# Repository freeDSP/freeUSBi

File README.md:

# freeUSBi

BOARD STATUS: READY TO BE BUILT

MAIN COORDINATOR: [thebadseeds](https://github.com/thebadseeds)

The freeUSBi is a low-budget real-time programming device for the freeDSP and other DSP boards from Analog Devices. It is based on a CY7C68013A MINI BOARD combined with an adapter PCB (printed circuit board) that adds the possibility of realtime programming.
It has the same features as the Analog Devices USB interface (EVAL-ADUSB2EBZ), such as changing parameters while already using the freeDSP or easy changes of the schematic in SigmaStudio. You also can write your program to the EEPROM.

Please refer to the documentation for more information.

## License

This work and all other materials under https://github.com/freeDSP are licensed under a <a rel="license" href="http://creativecommons.org/licenses/by-sa/4.0/legalcode">Creative Commons Attribution Share-Alike 4.0 license</a>. This allows for both personal and commercial derivative works, as long as they credit freeDSP and release their designs under the same license.

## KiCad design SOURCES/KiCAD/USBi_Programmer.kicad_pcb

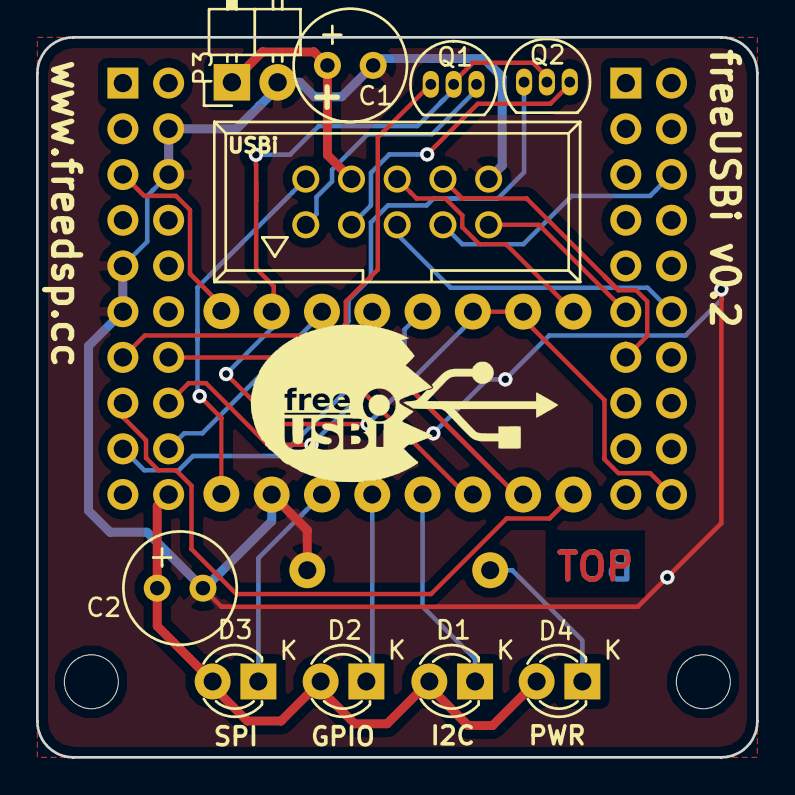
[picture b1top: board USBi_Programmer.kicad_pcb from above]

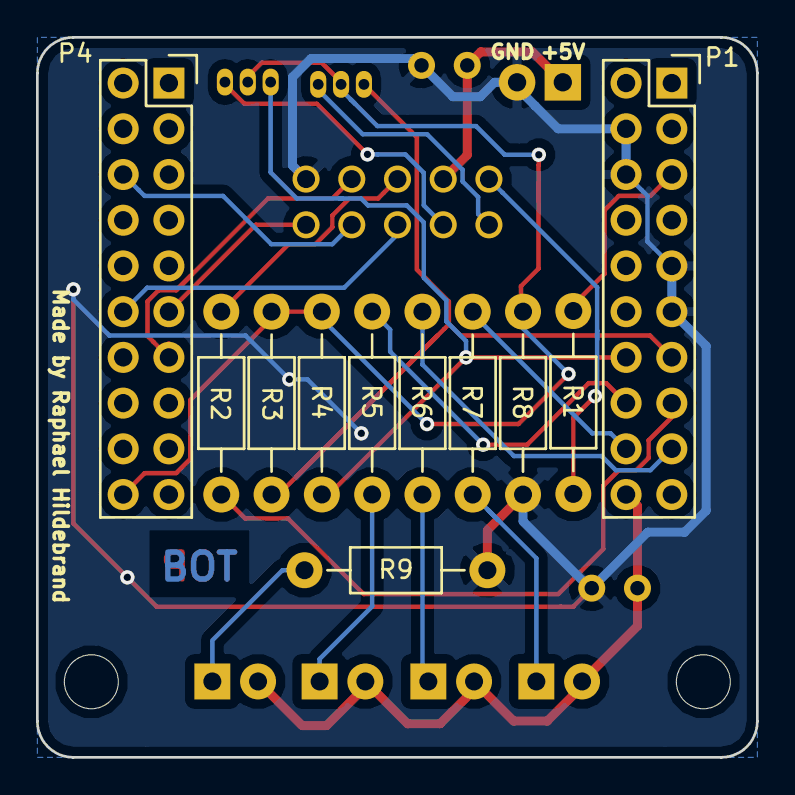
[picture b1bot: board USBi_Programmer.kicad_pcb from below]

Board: 2 copper layers, 40.0 x 40.0 mm, 21 parts (11 on the bottom side), 23 nets.

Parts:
C1, C2: 100u; Elko_vert_11.2x6.3mm_RM2.5_CopperClear
D1, D2, D3, D4: LED; LED-3MM
P1, P4: CONN_02X10; Socket_Strip_Straight_2x10
P2: CONN_02X05; VASCH5x2
P3: CONN_01X02; Pin_Header_Angled_1x02
Q1, Q2: Q_NMOS_DGS; TO-92_Inline_Narrow_Oval
R1: 49R9; Resistor_Horizontal_RM10mm
R2, R5, R6, R7, R9: 470R; Resistor_Horizontal_RM10mm
R3, R4: 10k; Resistor_Horizontal_RM10mm
R8: 1M; Resistor_Horizontal_RM10mm

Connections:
+3V3: C2.1, D1.2, D2.2, D3.2, D4.2, P1.20
+5VD: C1.1, P2.4, P3.1
BRD_~RESET: P2.6, R2.2
CCLK: P2.7, P4.6
CDATA: P2.8, P4.13
COUT: P2.5, P4.12
GND: C1.2, C2.2, P1.4, P1.6, P1.9, P1.11, P2.10, P3.2, R8.1, R9.2
LED_1: P1.16, R5.2
LED_2: P1.17, R6.2
LED_3: P1.18, R7.2
unnamed: D1.1, R5.1
unnamed: D2.1, R6.1
unnamed: D3.1, R7.1
unnamed: D4.1, R9.1
unnamed: P1.5, R1.1
unnamed: P1.15, R2.1
unnamed: P2.1, Q1.3
unnamed: P2.3, Q2.3
SCL: P1.13, Q1.1, R3.1
SDA: P1.14, Q2.1, R4.2
USB_CLK: P2.2, R1.2
USB_PWR_ON: P4.20, Q1.2, Q2.2, R3.2, R4.1, R8.2
~CLATCH1: P2.9, P4.11

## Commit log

2015-12-21 folder structure + initial sources V0.1
    added folder structure + initial sources V0.1
2015-12-21 Hardware configuration example for ADAU1701
2016-02-27 Create readme.md for testing link to GDOC documentation
2016-02-27 update link
2016-02-27 change text
2016-02-27 changed link
2016-04-21 Add drivers for Win10.
2016-04-25 tom test
2016-04-25 tom test deleted
2016-11-04 V0.2: Move holes & disconnect 2 pins from pinheader
    These pins usually had to be cut out from the main cypress board.
    Now that they're disconnected, there's no need anymore to cut them.
    Also the mounting holes didn't fit exactly to the holes on the cypress main board.
2016-11-30 Update schematic title to 'freeUSBi V0.2'
2016-11-30 Add PDF for freeUSBi V0.2 schematic
2016-11-30 Add PDF for freeUSBi V0.1 schematic
    This PDF is added for reference only. All
    new freeUSBi should be built with V0.2 or
    newer PCBs.
2016-11-30 Add gitignore & gitattributes
    These files were derived from the corresponding files
    within the freeDSP-KiCad-Library Github repository.
